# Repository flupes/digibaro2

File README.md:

# Digital Barograph v2 (with e-Paper display).

Status:
- all supporting custom libraries are now written and include tests
- main application functional
- schematic for board produced (one hole need fix)
- 3D [enclosure design with wooden plate](https://a360.co/2I1p0DZ) completed

*Picture of the final barograph*

There is also a [complete user manual](./brochure/brochure.pdf) with a lot of cool
build pictures.
(The brochure has been written in French because I offered a Digibaro to
my father for his 80th birthday, but it should not prevent you to have a look
at it!)

## Goal

Develop an open source digital barograph that does not require an external power
source, has a very low power consumption, and works on a boat independantly of
any wifi/cell connection.

## Motivation

I still believe that the barometric pressure is an essential decision making
tool when sailing. Displaying a graph rather than writing down single values
provides an instant evaluation of the trend.

The main idea is that the beautifull conventional mechanical barograph are not
suited for marine use (not resistant to vibration) and require a weekly paper
change.

The paper-electronic barographs aleviate this problem, but I remember that ours
was constantly jamming.

Several electronic barograph already exist on the market, but they all require
an external source of power (and are pricey).

## Rationale

Today you can have an app that will siphon the data from a nearby weather
station and display the barometric pressure in any format using your brillant
smartphone screen. And this is even not really necessary since having data
connectivity would allow to also get a full detailed weather forecast, much more
accurate, and covering a wider area, than what you could analyze yourself.

Despite our ever more connected world, I am old fashioned and like to believe
that having systems not relying on data flowing wirelessly to your boat can be
useful. It turns out that the fundamental building block for such a project is
readily available: several extremely accurate digital pressure sensors can be
sourced at low price (you may already have one in your cellphone).

I also wanted not to rely on an external source of power. This is not so much to
avoid battery drain (the most basic solar panel would provide more than enough),
but to avoid having extra wiring.

The final concept is that you would be able to leave the barograph on your boat,
and when coming back after six months, you would be able to read the barometric
pressure of the last few days because the barograph would keep collecting data.
Of course, this is probably superfluous since after leaving your boat six
months, you probably have more than 5 days of work before taking the sea again
(hence you could turn on the barograph).

At any rate, being a style exercise or a real need, the goal is to develop an
extremly low power barograph that could sustain at least six months on a set of
typical AA alkaline batteries!

There are few major difference between this project an my previous (never
completed) digibaro v1:

| Digibaro v1                 | Digibaro v2                   |
|-----------------------------|-------------------------------|
| Target low cost             | Cost is not the main priority |
| Classic UI with 5 buttons   | Mimimalist UI (analog feel)   |
| LCD screen                  | e-Paper display               |
| Only stores 5 days of data  | Long term recording (>20years)|
| Typical "maker" approach    | High reliability desired      |

## Hardware selection

The [first version of my digibaro](https://github.com/flupes/digibaro/) was
based one BMP085 sensor, a momochrome graphic LCD and an Arduino Pro-Mini
(3.3V). This version use modernized components.

The micro-controller is a ARM Cortex M0+ (SAMD21) packaged by RocketScream. This
board was selected because it was specifically designed for low power
applications (no extra LEDs, efficient regulator, etc.), and it provides 2MB of
flash memory on board.

The pressure sensor is a BOSH BME280. It provides excellent accuracy plus a
humidity and temperature sensor on the chip. The BMP680 would provide an extra
Volatile Organic gas detector, but a the cost of an extra complexity in managing
the sensor.

The display is based on a 400x300 black and white e-Paper system packaged by
Waveshare. E-paper display would seem ideal for this type of low power
application. However, since the refresh rate is so slow (~4s for this particular
display), updating the display takes a significant amount energy. There is a
cutting-point between a LCD (that refresh very quickly and consume very low
power in standby) and an e-Paper display that depends on the number of refresh
per day. Still, for this application, the e-Paper provides a nice, more natural,
look.

## Reference products

[Bohlken BG1512](http://www.bohlken.net/bg/bg1512_en.htm)
- Require external power source
- 10mA without backlight
- Retired
- ~300 Euro

[Aquatech DBX2](https://www.digitalbarograph.com/)
- Require external power source
- 20mA @ 5V DC (160mA with LED backlight)
- Storm alarm
- Factory calibrated
- [DBX2 User Manual](https://www.digitalbarograph.com/pdfs/DBX2_MANUAL_V1W.pdf)  
- ~$500

[NASA Meteoman](https://www.nasamarine.com/product/meteoman/)
- Consumes 100mA (without backlight), require external source of power
- Pressure change graph
- [Meteoman screenshots and discussion](http://www.ybw.com/forums/showthread.php?452897-Calling-Weather-Experts-What-do-you-Need-in-a-Barograph)
- ~$200

[Raber Barograf](http://www.barograph.ch/Barograph_E/barograph.html)
- Paper recording :-)
- Swiss made ;-)
- One single C type battery for a year!
- Very cool, however we had a similar model that jammed quite often.  
- [Meteograf User Manual](http://www.barograph.ch/Downloads/BA_Meteograf_Englisch_2.4.pdf)  
- ~$900 without case

## Related projects

In May 2019, I just discovered this: [Arduino + BMP085 Barograph from PauloDevelo on Arbatus](https://www.arbutus.ecogium.fr/the-boat/electronic-equipment/barograph-arbutus/).

<!-- 
Code at: https://github.com/PauloDevelo/Barograph/blob/master/src/barograph.ino

This is similar to to what I started to develop with v1 of digibaro. However,
PauloDevelo chose a much simpler route: it is again powered from the boat
batteries (so not need for sleep mode), there is no RTC, no real concept of time
series, no user interface per say. This allowed him to complete the project
(unlike my digibaro v1). Congratulations! In addition, he created a nice wooden
enclosure.
-->

## Build

Currently digibaro2 is built using platformIO. This mainly constrains the
directory structure. Each test program show in the comments the command
to build it. The main application uses the platormio.ini definitions and
calls an extra script (version.py) to inject the git hash. This last part
is not directly portable to another build system.

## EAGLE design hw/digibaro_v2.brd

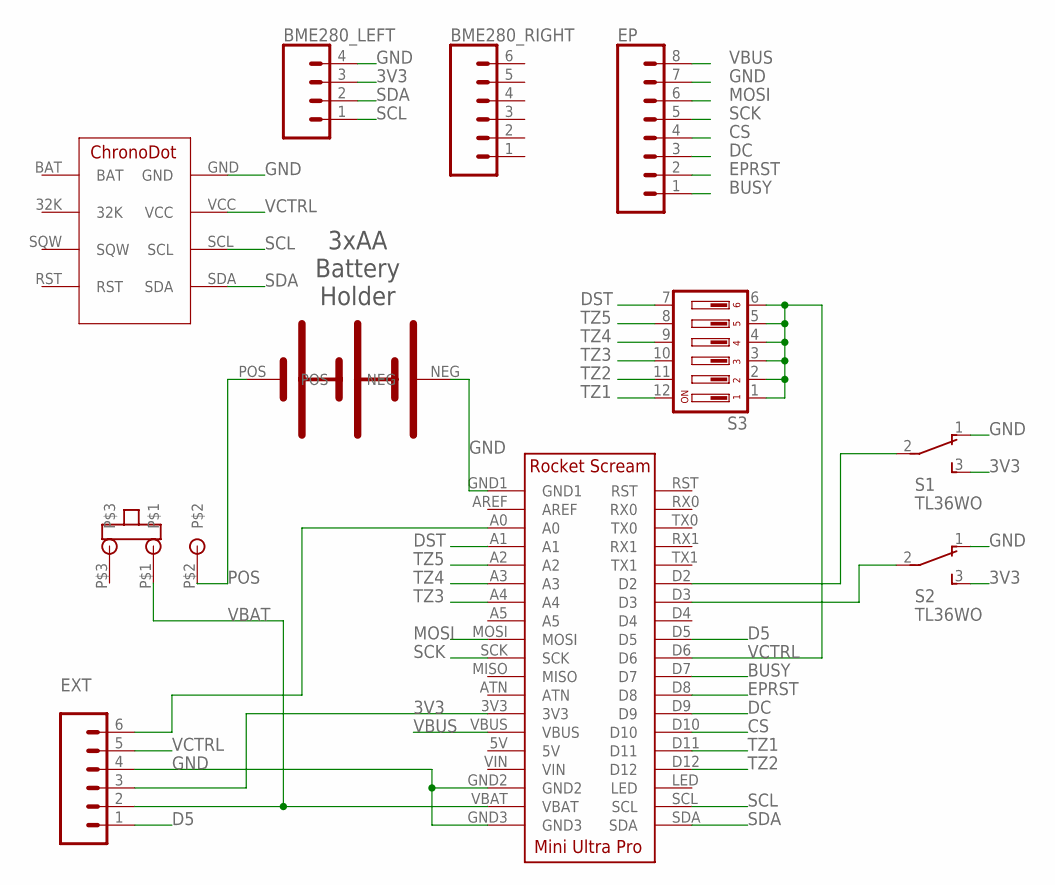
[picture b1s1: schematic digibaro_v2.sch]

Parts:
BME280_LEFT: CONN_04; 1X04
BME280_RIGHT: CONN_06SILK_FEMALE_PTH; 1X06
EP: CONN_08"; 1X08
EXT: CONN_06SILK_FEMALE_PTH; 1X06
S1, S2: TL36WO; TL3XWO
S3: DA06; DA-06
U$1: BATTERY-HOLDER_3AA
U$2: SLIDE-SWITCHNKKMINIATURE; MS12ANG03
U$3: ULTRA-MINI-PRO; ULTRA-MINI-PRO_RECEIVER
U$4: CHRONODOT; CHRONODOT_RECEIVER

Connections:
3V3: BME280_LEFT.3, EXT.3, S1.3 (S), S2.3 (S), U$3.3V3
A0: EXT.6, U$3.A0
BUSY: EP.1, U$3.D7
CS: EP.4, U$3.D10
D5: EXT.1, U$3.D5
DC: EP.3, U$3.D9
DST: S3.7, U$3.A1
EPRST: EP.2, U$3.D8
GND: BME280_LEFT.4, EP.7, EXT.4, S1.1 (O), S2.1 (O), U$1.NEG, U$3.GND1, U$3.GND2, U$3.GND3, U$4.GND
MOSI: EP.6, U$3.MOSI
unnamed: S1.2, U$3.D2
unnamed: S2.2, U$3.D3
POS: U$1.POS, U$2.P$2
SCK: EP.5, U$3.SCK
SCL: BME280_LEFT.1, U$3.SCL, U$4.SCL
SDA: BME280_LEFT.2, U$3.SDA, U$4.SDA
TZ1: S3.12, U$3.D11
TZ2: S3.11, U$3.D12
TZ3: S3.10, U$3.A4
TZ4: S3.9, U$3.A3
TZ5: S3.8, U$3.A2
VBAT: EXT.2, U$2.P$1, U$3.VBAT
VBUS: EP.8, U$3.VBUS
VCTRL: EXT.5, S3.1, S3.2, S3.3, S3.4, S3.5, S3.6, U$3.D6, U$4.VCC

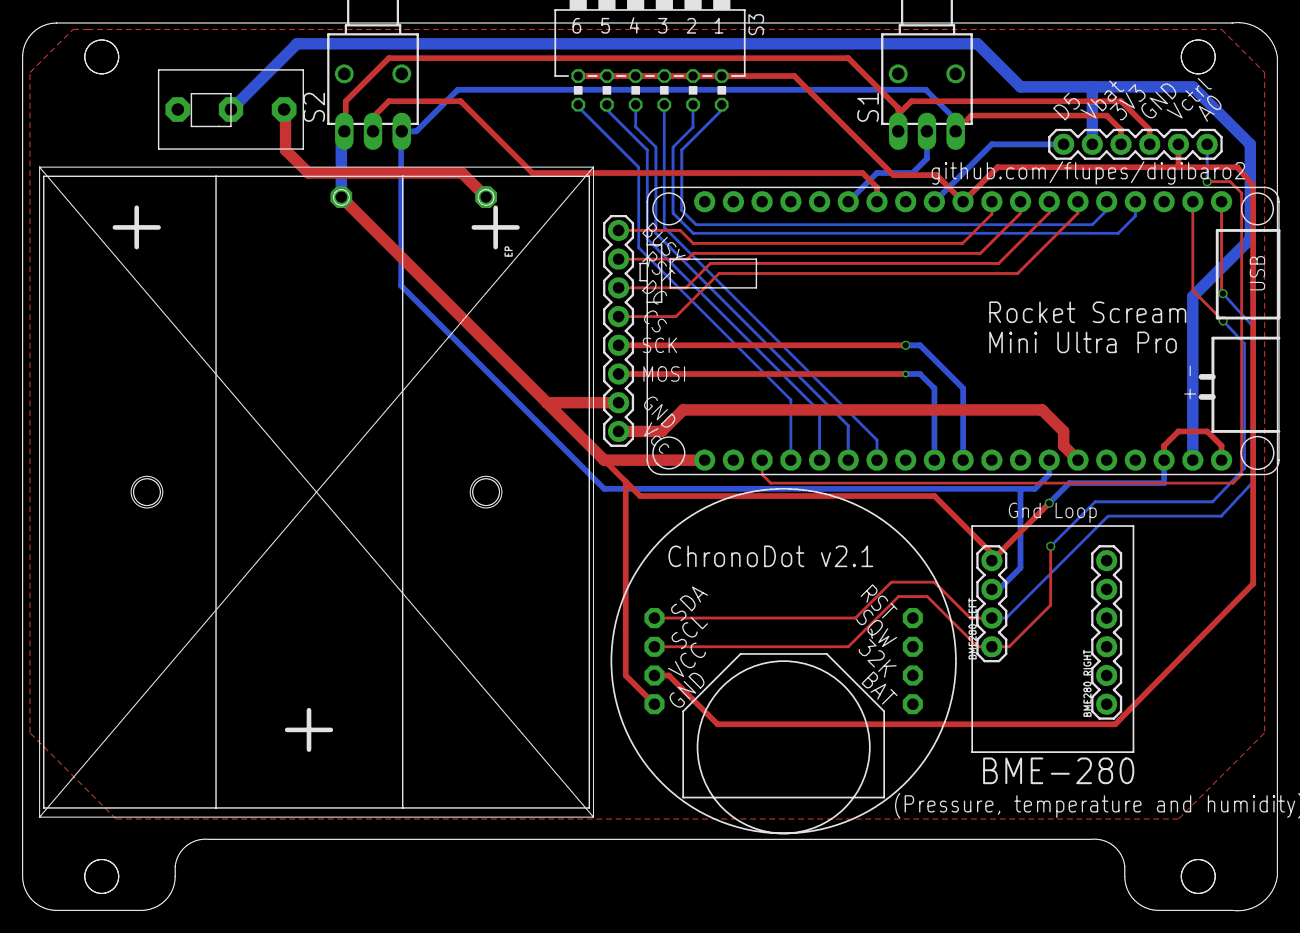
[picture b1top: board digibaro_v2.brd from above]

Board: 2 copper layers, 111.0 x 78.6 mm, 11 parts (0 on the bottom side), 24 nets.

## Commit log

2019-03-17 started constructing a sample data structure (untested)
2019-03-17 removed superflous test for index retrieval
2019-03-17 renamed file matching class name
2019-03-17 added required libraries as submodules
2019-03-17 updated to latest version
2019-03-17 Example for robust index storage on the Flash memory
2019-03-17 added the robust index system and test program
2019-03-19 starting testing sample packing... bug for negative numbers
2019-03-19 added a program to test bit packing compactness on the SAMD21
2019-03-20 added documentation and some helper methods
2019-03-20 packing works now with signed int16
2019-03-21 fixed negative number packing on 14 bits for good
2019-03-21 starting project
2019-03-23 trying to fix the submodules
2019-03-23 fixing the .gitmodule
2019-03-23 added the correct version of the driver!
2019-03-23 Added custom BME280 library and test program
2019-03-24 added RTC submodule
2019-03-25 pushed to latest
2019-03-25 removed wrong library
2019-03-25 re-organize code into more libraries to manage better the dependencies
2019-03-31 packed two more bits in the header
2019-03-31 fixed signed integer mismatch
2019-03-31 fixed documentation
2019-03-31 added sample collector and reader test programs
2019-04-14 added some collected data and associated plot
2019-04-15 made the test more robust
2019-04-15 moved test into its own subdir
2019-04-16 fix a few bugs in RobustIndex and better testing: functional now
2019-04-16 added program to verify the Int24Crc8 functionalities
2019-04-16 test Adafruit on Waveshare display and multiple fonts
2019-04-17 added constant for time resolution
2019-04-17 added header guards
2019-04-17 added utility to support writing/reading time serie samples
2019-04-17 modify the test program to use PermanentSamples
2019-04-17 greatly simplified
2019-04-17 use small memory area for debugging
2019-04-17 use correctly indexed sample (starting at 0)
2019-04-17 modified test to use the new PermanentSamples class
2019-04-18 moved classes to independant libraries
2019-04-18 moved too much code from the header to the implementation, and added serialization
2019-04-19 moved shared header out of library
2019-04-19 added raw serialization
2019-04-19 corrected typo
2019-04-19 Skip writing an index by default after initializing
2019-04-19 adapted test to updated class
2019-04-19 added new class to support rotating samples
2019-04-21 added iterator and more robust test
2019-04-21 added a period between hourly samples and a default constructor with and invalid sample
2019-04-21 return the last index when initializing
2019-04-21 added methods to retrieve data
2019-04-21 removed some debugging print statements
2019-04-21 added pretty print method
2019-04-21 Created base collecting program
2019-04-21 executable to wipe out the permanent samples
2019-04-21 cleaned up
2019-04-23 bug fixes
2019-04-23 correct extra space in build command
2019-04-23 SAMD21 sleep test functional with I2C and SPI devices (25uA)
2019-04-27 example using the Waveshare hardware library with the AdafruitGfx software buffer
2019-04-28 use a different flash address when testing
2019-04-28 improved testing
2019-04-28 printout management
2019-04-28 simple sample generator added for testing
2019-04-28 started program to read samples in the ring buffer
2019-04-29 added a fork of Adafruit GFX to the libarries
2019-04-29 added documentation
2019-04-29 added a reverse iterator
2019-04-29 bumped up to latest
2019-04-29 Added WaveShare code. See note below.
    Purpose: avoid to have a submodule pulling the full WaveShare repo (which did not exist
    when the project was started anyway). The code here is ONLY for the 4.2in (400x300)
    B&W (revision A) of the e-Paper display, with ONLY the Arduino code (no demo).
    Source: https://www.waveshare.com/wiki/4.2inch_e-Paper_Module
    License: WaveShare custom (see any header file)
    Current Git repo: https://github.com/waveshare/e-Paper/tree/master/4.2inch_e-paper_code
2019-04-29 removes 100 lines (manually) to creates "holes" in the dataset
2019-04-29 added class to manage samples from flash into RAM for fast display
2019-04-29 fixed offset bug
2019-05-06 Create a better deep sleep mode
2019-05-06 added e-paper in the mix, and still get 25uA sleeping!
2019-05-06 include correct header
2019-05-06 removed some printout
2019-05-08 added option to facilitate debugging
2019-05-08 reformatted for better lisibility
2019-05-08 added debug info
2019-05-12 added debug print functions
2019-05-12 removed that memory map switch
2019-05-12 separated classes in two files
2019-05-12 fixed major bug in GetCounterAt and made less dependant of memory map
2019-05-12 adapted tests
2019-05-12 documented, fixed and test test
2019-05-12 re-worked display_samples
2019-05-12 moved test to appropriate location
2019-05-12 performance for display sample working again
2019-05-12 better implementation that averages samples (if available) when filling the buffer
2019-05-13 put back limits computation
2019-05-13 Added graphing to display samples
2019-05-17 added Heckbert tick marks finding for graph labels
2019-05-17 added a variation of graphing
2019-05-17 moved GraphSamples into its own library for cleaner dependencies
2019-05-20 trying to add an external interrupt (not working yet)
2019-05-20 minor fixes
2019-05-20 starting to draw some real graphs
2019-05-20 mute some warnings
2019-05-21 external switch wake the board up correctly from deepsleep :-)
2019-05-21 disabled flash to save more, added circuit doc
2019-05-21 added new test for low power dip switch
2019-05-22 fixed switch description
2019-05-27 added altitude correction
2019-05-27 added altitude
2019-05-27 started some project documentation
2019-05-27 corrected typos
2019-05-27 improved products section
2019-05-27 added current Eagle design
2019-05-27 more info
2019-05-29 bumped up submodules
2019-05-29 mode documentation
2019-05-29 added diagram for main digibaro classes
2019-05-30 fixed schematic, corrected footprint (switch + rocket scream) and improved layout
2019-06-03 Minimize power and still manage correctly buses
    Consumption in standby: 22uA (4.5V)
    Works correctly for all conditions:
    - bare board (nor external RTC), on board flash (SPI)
    - no display but RTC in I2C
    - e-Paper display on SPI + RTC on I2C
2019-06-03 started main app
2019-06-04 skeleton of app working correctly with standby
2019-06-05 added debug information and disabled flash sleep for now
2019-06-05 added the external switches wakup
2019-06-12 added long duration WDT
2019-06-13 added utility to write timestamped debug message to flash
2019-06-23 more protection
2019-06-23 added wdt to app and log debug to flash
2019-06-23 added logging to flash
2019-06-23 moved flash debug into its own library
2019-06-23 re-work the memory map
2019-06-23 draw graphs with y labels to the right and x labels
2019-06-23 fixed doc
2019-06-23 try to integrate Ben Krasnov mods
2019-06-23 allow OTP or Registrer LUT + allow refresh with OLD data
2019-06-23 try to optimize the display use (send old data)
2019-06-23 obsolete test (now in GraphSamples)
2019-06-23 added foreground/background color selection
2019-06-24 changed pointer to reference for more safety
2019-06-24 scale the Y axis for series with no variation (or quasi empty)
2019-06-24 main app with draft of displays
2019-06-25 inject git hash into the main application
2019-06-25 added DIP switch support for settings
2019-06-25 fixed DST and reverse switch
2019-06-26 restore IfSleep to minimize current draw in standby
2019-06-27 fixed switch mode and tuned periods
2019-06-27 added compile infor
2019-06-27 more plots
2019-06-27 added missing library to compile command
2019-06-27 updated sumbmodules
2019-06-27 added real stats to display
2019-06-27 better stat display (new font and first element)
2019-07-01 added a splash screen for VAI
2019-07-02 added graph header
2019-07-02 comment out unused variable
2019-07-02 added warning message type
2019-07-02 added debug with str argument
2019-07-02 increase default graph height
2019-07-08 bumped up version with committed fonts
2019-07-08 declare the maximum allowed pressure
2019-07-08 Added basic statistics computation
2019-07-08 corrected class diagram
2019-07-08 simplified the SLOC measure
2019-07-08 try to make the vbat sense work: no success
2019-07-08 Added more statistics to the INFO screen
2019-07-08 forgotten file
2019-07-08 bumped up to get latest version from Adafruit
2019-07-08 do not mess up with utc (need to fix RTClib\!)
2019-07-16 use fixed scale by default
2019-07-16 use proper case for include
2019-07-16 shrink the scale to more normal weather
2019-07-16 adjust the graph size to display better with default scale
2019-07-27 fixed reversed logic
2019-09-14 added brochure files
2019-09-14 added pic of finished project
2019-09-14 Updated with current status
2019-09-14 Added link to the 3D model
2022-02-20 adapted for recent toolchain
2022-02-20 adapted for python3
2022-02-28 added command for linux testing
2022-02-28 added the specific version of the platform to use
2022-02-28 fixed (for good?) the paper limits
2022-03-01 added the option to rotate the dislpay 180deg at boot
2022-03-01 more debug flags
2022-04-11 added firmware for ease of flashing without pio
2024-06-08 clean header from code
2024-06-09 removed tagged platform version
2024-06-10 Plots data retrieved from a digibaro flash
2024-12-03 Start with the display flipped vertically (switches pointed upwards)

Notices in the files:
parts and their libraries:
SparkFun-Connectors: Licensing: Creative Commons ShareAlike 4.0 International - https://creativecommons.org/licenses/by-sa/4.0
